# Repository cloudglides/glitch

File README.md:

<h1 align="center">
  GLITCH
  <br>
</h1>
<h4 align="center">
a wearable conference badge PCB
</h4>
<div align="center">

</div>
<p align="center">
  <a href="#key-features">Key Features</a> •
  <a href="#pcb">PCB</a> •
  <a href="#credits">Credits</a> 
</p>

<p>&nbsp;</p>

# GLITCH

GLITCH is a lanyard badge in the style of the tech-conference PCB badges, built around an ESP32-C3 with an OLED display, 5 buttons and a row of RGB LEDs, running off a LiPo that charges over USB-C.

the front is the part you look at: the silkscreen art, the LEDs, the display and the buttons. all the actual electronics live on the back, along with a spot to tape the battery.

to build your own, grab the KiCad files, check out the schematic and BOM, and send the Gerber files to your preferred PCB manufacturer. the ESP32-C3 is flashed straight over USB-C, hold BOOT and tap RST to get into the bootloader.

## Key Features

* **ESP32-C3-WROOM-02** module with WiFi and Bluetooth LE
* **USB-C** for charging, flashing and serial (native USB, no bridge chip)
* **0.96" SSD1306 OLED** on a 4 pin I2C socket
* **6x WS2812B** addressable RGB LEDs
* **5 front buttons** (A, B, C, up, down) plus reset and boot on the back
* **LiPo charging** using TP4054 (~200mA) with a charge LED
* **Power path** using AO3401A and a Schottky, so USB takes over when plugged in
* **3.3V regulation** using ME6211
* **Power switch** and JST-PH battery connector
* **2-layer PCB**, 80 x 100 mm, with lanyard slots
* every part has an **LCSC** part number

## PCB

generated for KiCad 10 as a 2-layer board. the layout has the LEDs, display socket and buttons on the front, and the ESP32 module, USB-C, charger, regulator and battery connector on the back.

the ESP32 antenna sits at the left edge of the board with a copper keepout around it. the USB-C connector is at the bottom edge and the power switch pokes out of the side. power nets are routed at 0.5mm, everything else at 0.25mm, with ground pours on both layers.

## Files

the repository includes the KiCad project files, schematic, BOM, Gerber exports,

* `pcb/` KiCad project
* `docs/` schematic PDF
* `production/` Gerbers and CPL
* `BOM.csv` bill of materials with LCSC part numbers
* `journal.md` build log

everything is open source, feel free to take a look, modify it or build your own!

### Schematic

---

### PCB Layers

#### F.CU

#### B.CU

---

### Board Views

#### Front

#### Back

## Before you build

* the board has not been manufactured or tested yet, it passes ERC and DRC and thats it
* check your LiPo polarity against the + and - on the silkscreen, JST-PH batteries are not all wired the same
* the OLED socket is GND / VCC / SCL / SDA, some modules swap the first two
* keep LED brightness low when running from USB without a battery

## Credits

This project uses:
- [KiCad](https://www.kicad.org/)

### ZINE

## License

GPL

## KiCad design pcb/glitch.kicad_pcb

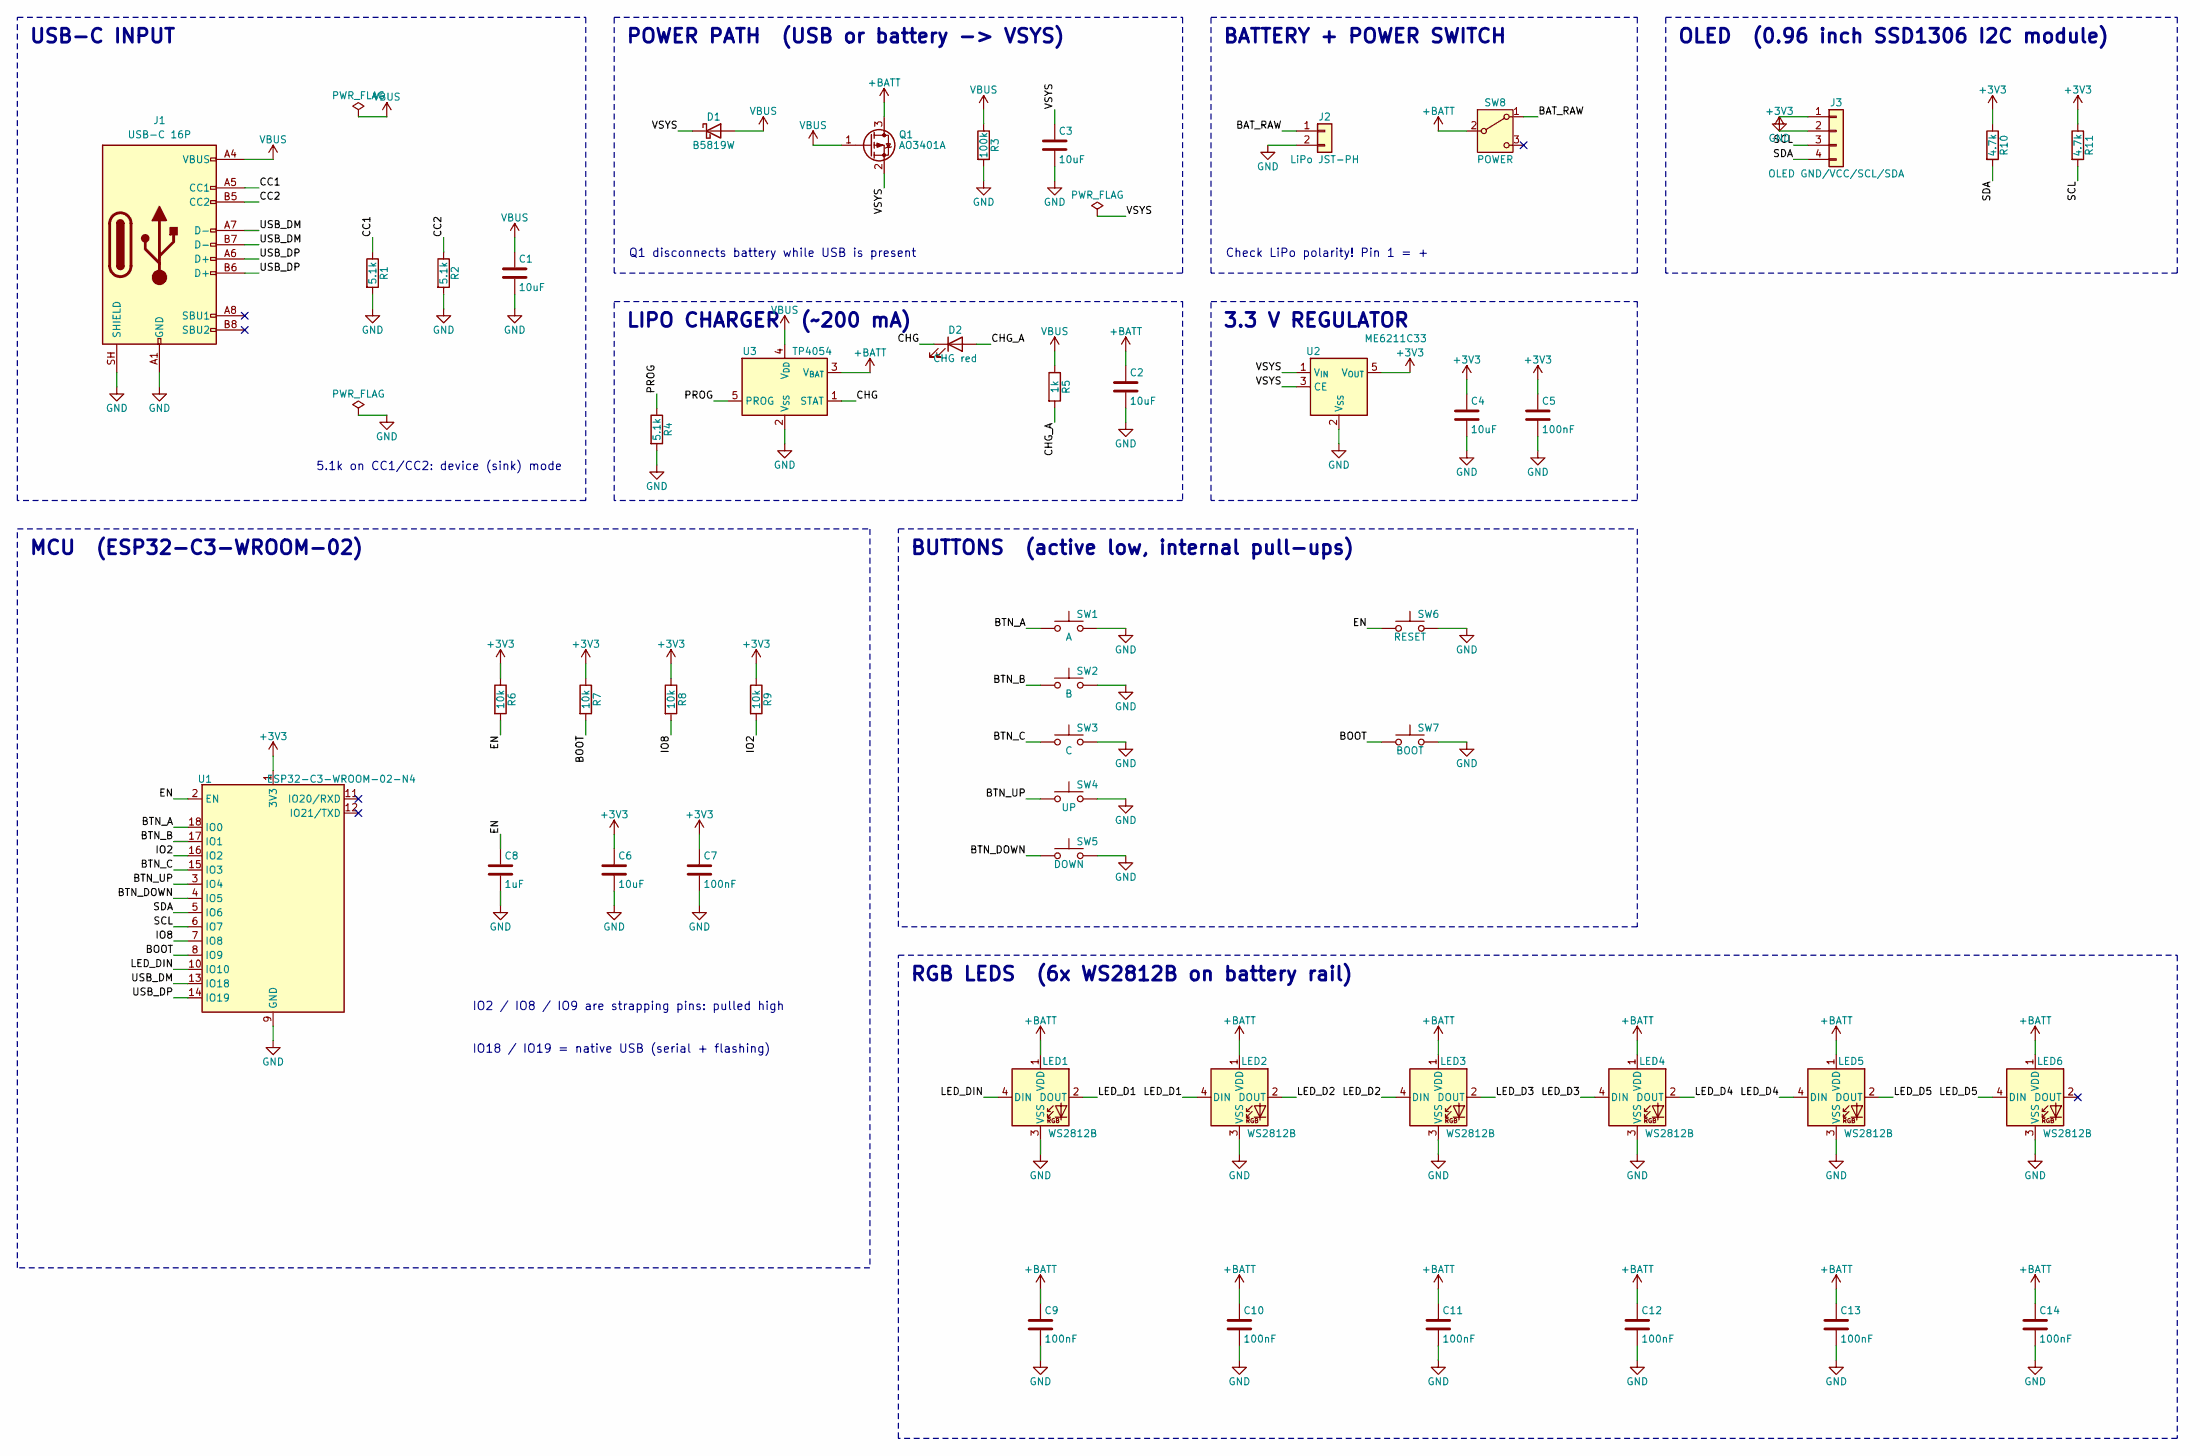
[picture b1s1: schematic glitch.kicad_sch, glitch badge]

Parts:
C1, C2, C3, C4, C6: 10uF; C_0603_1608Metric; LCSC C19702
C5, C7, C9, C10, C11, C12, C13, C14: 100nF; C_0603_1608Metric; LCSC C14663
C8: 1uF; C_0603_1608Metric; LCSC C15849
D1: B5819W; D_SOD-123; LCSC C8598
D2: CHG red; LED_0603_1608Metric; LCSC C2286
J1: USB-C 16P; USB_C_Receptacle_HRO_TYPE-C-31-M-12; LCSC C165948
J2: LiPo JST-PH; JST_PH_S2B-PH-SM4-TB_1x02-1MP_P2.00mm_Horizontal; LCSC C295747
J3: OLED GND/VCC/SCL/SDA; PinSocket_1x04_P2.54mm_Vertical; LCSC C2718488
LED1, LED2, LED3, LED4, LED5, LED6: WS2812B; LED_WS2812B_PLCC4_5.0x5.0mm_P3.2mm; LCSC C114586
Q1: AO3401A; SOT-23; LCSC C15127
R1, R2, R4: 5.1k; R_0603_1608Metric; LCSC C23186
R3: 100k; R_0603_1608Metric; LCSC C25803
R5: 1k; R_0603_1608Metric; LCSC C21190
R6, R7, R8, R9: 10k; R_0603_1608Metric; LCSC C25804
R10, R11: 4.7k; R_0603_1608Metric; LCSC C23162
SW1: A; SW_Push_1P1T_XKB_TS-1187A; LCSC C318884
SW2: B; SW_Push_1P1T_XKB_TS-1187A; LCSC C318884
SW3: C; SW_Push_1P1T_XKB_TS-1187A; LCSC C318884
SW4: UP; SW_Push_1P1T_XKB_TS-1187A; LCSC C318884
SW5: DOWN; SW_Push_1P1T_XKB_TS-1187A; LCSC C318884
SW6: RESET; SW_Push_1P1T_XKB_TS-1187A; LCSC C318884
SW7: BOOT; SW_Push_1P1T_XKB_TS-1187A; LCSC C318884
SW8: POWER; SW_SPDT_Shouhan_MSK12C02; LCSC C431540
U1: ESP32-C3-WROOM-02-N4; ESP32-C3-WROOM-02; LCSC C2934560
U2: ME6211C33; SOT-23-5; LCSC C82942
U3: TP4054; SOT-23-5; LCSC C32574

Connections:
+3V3: C4.1, C5.1, C6.1, C7.1, J3.2, R6.1, R7.1, R8.1, R9.1, R10.1, R11.1, U1.1 (3V3), U2.5 (V_{OUT})
+BATT: C2.1, C9.1, C10.1, C11.1, C12.1, C13.1, C14.1, LED1.1 (VDD), LED2.1 (VDD), LED3.1 (VDD), LED4.1 (VDD), LED5.1 (VDD), LED6.1 (VDD), Q1.3 (D), SW8.2 (B), U3.3 (V_{BAT})
/BAT_RAW: J2.1, SW8.1 (A)
/BOOT: R7.2, SW7.1, U1.8 (IO9)
/BTN_A: SW1.1, U1.18 (IO0)
/BTN_B: SW2.1, U1.17 (IO1)
/BTN_C: SW3.1, U1.15 (IO3)
/BTN_DOWN: SW5.1, U1.4 (IO5)
/BTN_UP: SW4.1, U1.3 (IO4)
/CC1: J1.A5 (CC1), R1.1
/CC2: J1.B5 (CC2), R2.1
/CHG: D2.1 (K), U3.1 (STAT)
/CHG_A: D2.2 (A), R5.2
/EN: C8.1, R6.2, SW6.1, U1.2 (EN)
/IO2: R9.2, U1.16 (IO2)
/IO8: R8.2, U1.7 (IO8)
/LED_D1: LED1.2 (DOUT), LED2.4 (DIN)
/LED_D2: LED2.2 (DOUT), LED3.4 (DIN)
/LED_D3: LED3.2 (DOUT), LED4.4 (DIN)
/LED_D4: LED4.2 (DOUT), LED5.4 (DIN)
/LED_D5: LED5.2 (DOUT), LED6.4 (DIN)
/LED_DIN: LED1.4 (DIN), U1.10 (IO10)
/PROG: R4.1, U3.5 (PROG)
/SCL: J3.3, R11.2, U1.6 (IO7)
/SDA: J3.4, R10.2, U1.5 (IO6)
/USB_DM: J1.A7 (D-), J1.B7 (D-), U1.13 (IO18)
/USB_DP: J1.A6 (D+), J1.B6 (D+), U1.14 (IO19)
/VSYS: C3.1, D1.1 (K), Q1.2 (S), U2.1 (V_{IN}), U2.3 (CE)
GND: C1.2, C2.2, C3.2, C4.2, C5.2, C6.2, C7.2, C8.2, C9.2, C10.2, C11.2, C12.2, C13.2, C14.2, J1.A1 (GND), J1.A12 (GND), J1.B1 (GND), J1.B12 (GND), J1.SH (SHIELD), J2.2, J3.1, LED1.3 (VSS), LED2.3 (VSS), LED3.3 (VSS), LED4.3 (VSS), LED5.3 (VSS), LED6.3 (VSS), R1.2, R2.2, R3.2, R4.2, SW1.2, SW2.2, SW3.2, SW4.2, SW5.2, SW6.2, SW7.2, U1.9 (GND), U1.19 (GND), U2.2 (V_{SS}), U3.2 (V_{SS})
VBUS: C1.1, D1.2 (A), J1.A4 (VBUS), J1.A9 (VBUS), J1.B4 (VBUS), J1.B9 (VBUS), Q1.1 (G), R3.1, R5.1, U3.4 (V_{DD})

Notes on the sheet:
USB-C INPUT
5.1k on CC1/CC2: device (sink) mode
POWER PATH (USB or battery -> VSYS)
Q1 disconnects battery while USB is present
LIPO CHARGER (~200 mA)
BATTERY + POWER SWITCH
Check LiPo polarity! Pin 1 = +
3.3 V REGULATOR
OLED (0.96 inch SSD1306 I2C module)
MCU (ESP32-C3-WROOM-02)
IO2 / IO8 / IO9 are strapping pins: pulled high
IO18 / IO19 = native USB (serial + flashing)
BUTTONS (active low, internal pull-ups)
RGB LEDS (6x WS2812B on battery rail)

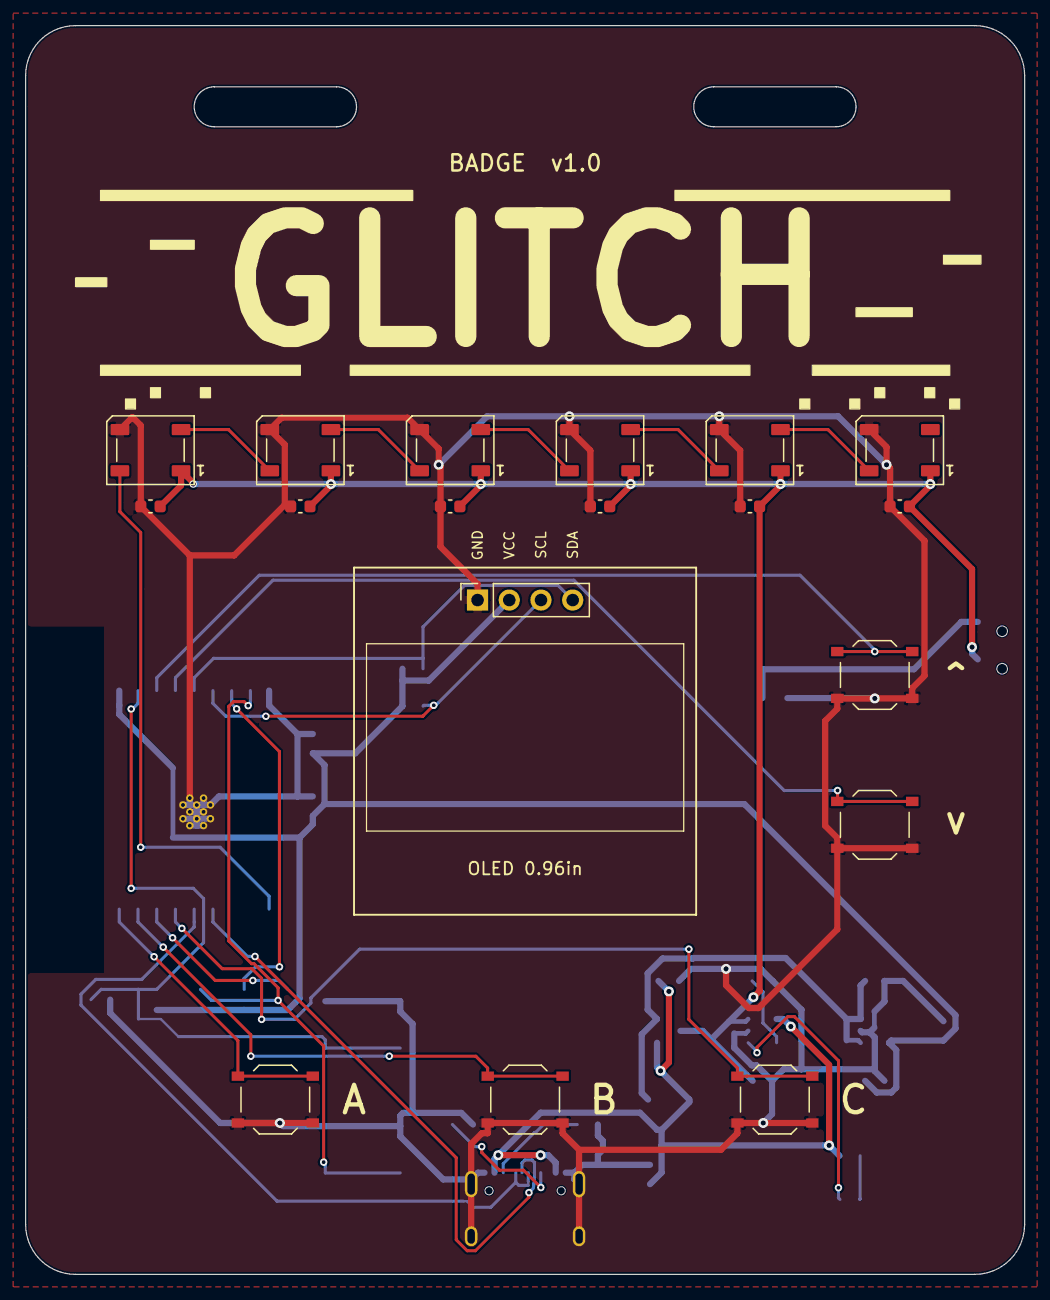
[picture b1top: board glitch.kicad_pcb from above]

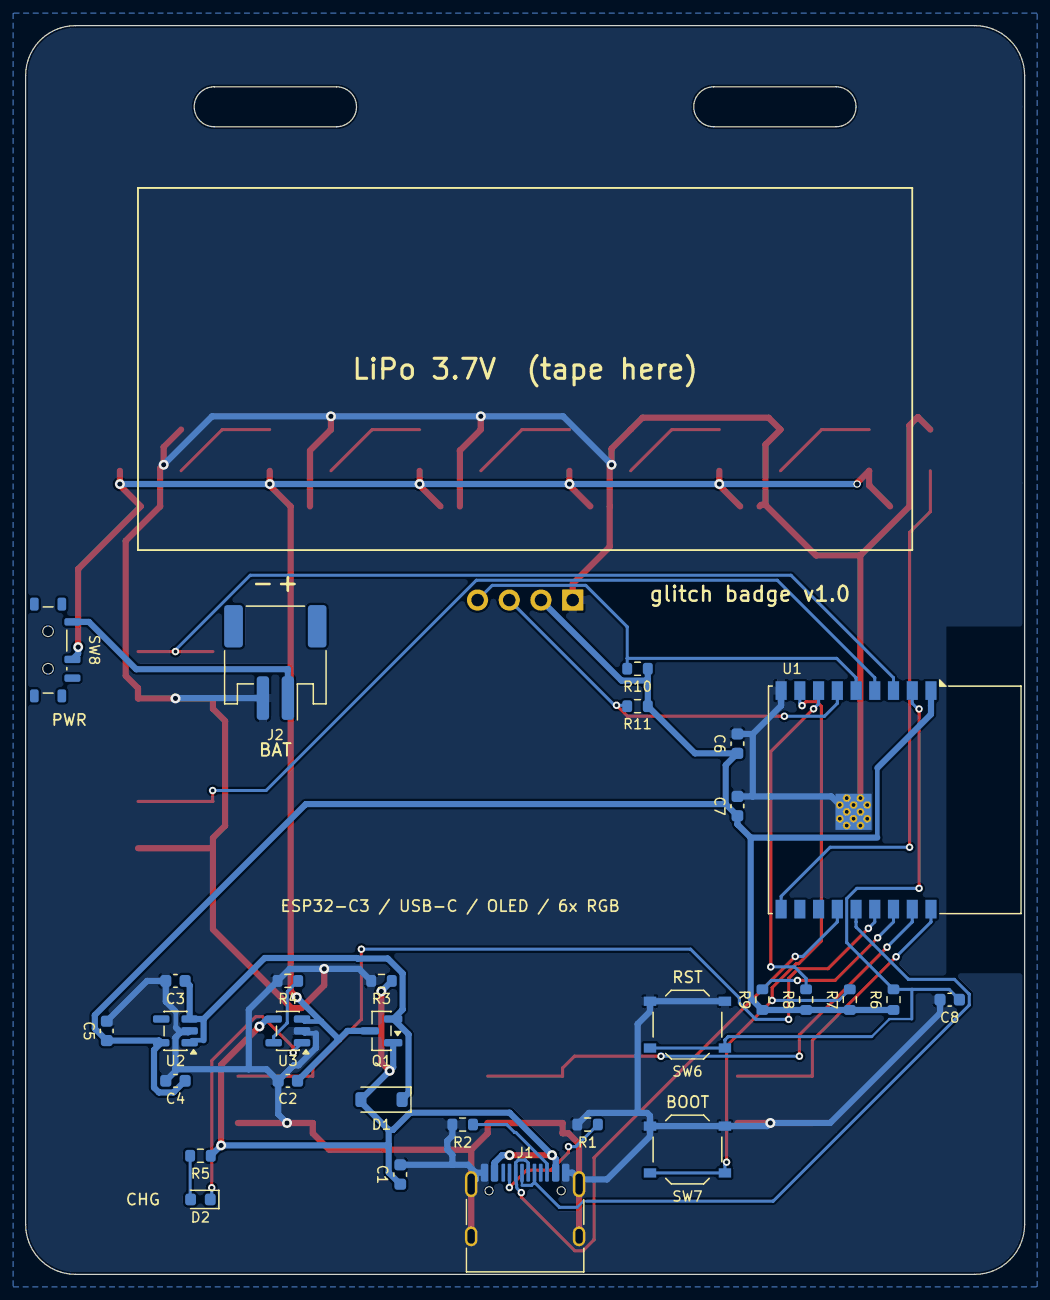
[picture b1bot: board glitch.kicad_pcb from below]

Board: 2 copper layers, 80.0 x 100.0 mm, 48 parts (30 on the bottom side), 30 nets.

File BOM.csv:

Comment,Designator,Footprint,LCSC Part #,Quantity
10uF,"C1,C2,C3,C4,C6",C_0603_1608Metric,C19702,5
100nF,"C5,C7,C9,C10,C11,C12,C13,C14",C_0603_1608Metric,C14663,8
1uF,C8,C_0603_1608Metric,C15849,1
B5819W,D1,D_SOD-123,C8598,1
CHG red,D2,LED_0603_1608Metric,C2286,1
USB-C 16P,J1,USB_C_Receptacle_HRO_TYPE-C-31-M-12,C165948,1
LiPo JST-PH,J2,JST_PH_S2B-PH-SM4-TB_1x02-1MP_P2.00mm_Horizontal,C295747,1
OLED GND/VCC/SCL/SDA,J3,PinSocket_1x04_P2.54mm_Vertical,C2718488,1
WS2812B,"LED1,LED2,LED3,LED4,LED5,LED6",LED_WS2812B_PLCC4_5.0x5.0mm_P3.2mm,C114586,6
AO3401A,Q1,SOT-23,C15127,1
5.1k,"R1,R2,R4",R_0603_1608Metric,C23186,3
100k,R3,R_0603_1608Metric,C25803,1
1k,R5,R_0603_1608Metric,C21190,1
10k,"R6,R7,R8,R9",R_0603_1608Metric,C25804,4
4.7k,"R10,R11",R_0603_1608Metric,C23162,2
A,SW1,SW_Push_1P1T_XKB_TS-1187A,C318884,1
B,SW2,SW_Push_1P1T_XKB_TS-1187A,C318884,1
C,SW3,SW_Push_1P1T_XKB_TS-1187A,C318884,1
UP,SW4,SW_Push_1P1T_XKB_TS-1187A,C318884,1
DOWN,SW5,SW_Push_1P1T_XKB_TS-1187A,C318884,1
RESET,SW6,SW_Push_1P1T_XKB_TS-1187A,C318884,1
BOOT,SW7,SW_Push_1P1T_XKB_TS-1187A,C318884,1
POWER,SW8,SW_SPDT_Shouhan_MSK12C02,C431540,1
ESP32-C3-WROOM-02-N4,U1,ESP32-C3-WROOM-02,C2934560,1
ME6211C33,U2,SOT-23-5,C82942,1
TP4054,U3,SOT-23-5,C32574,1
